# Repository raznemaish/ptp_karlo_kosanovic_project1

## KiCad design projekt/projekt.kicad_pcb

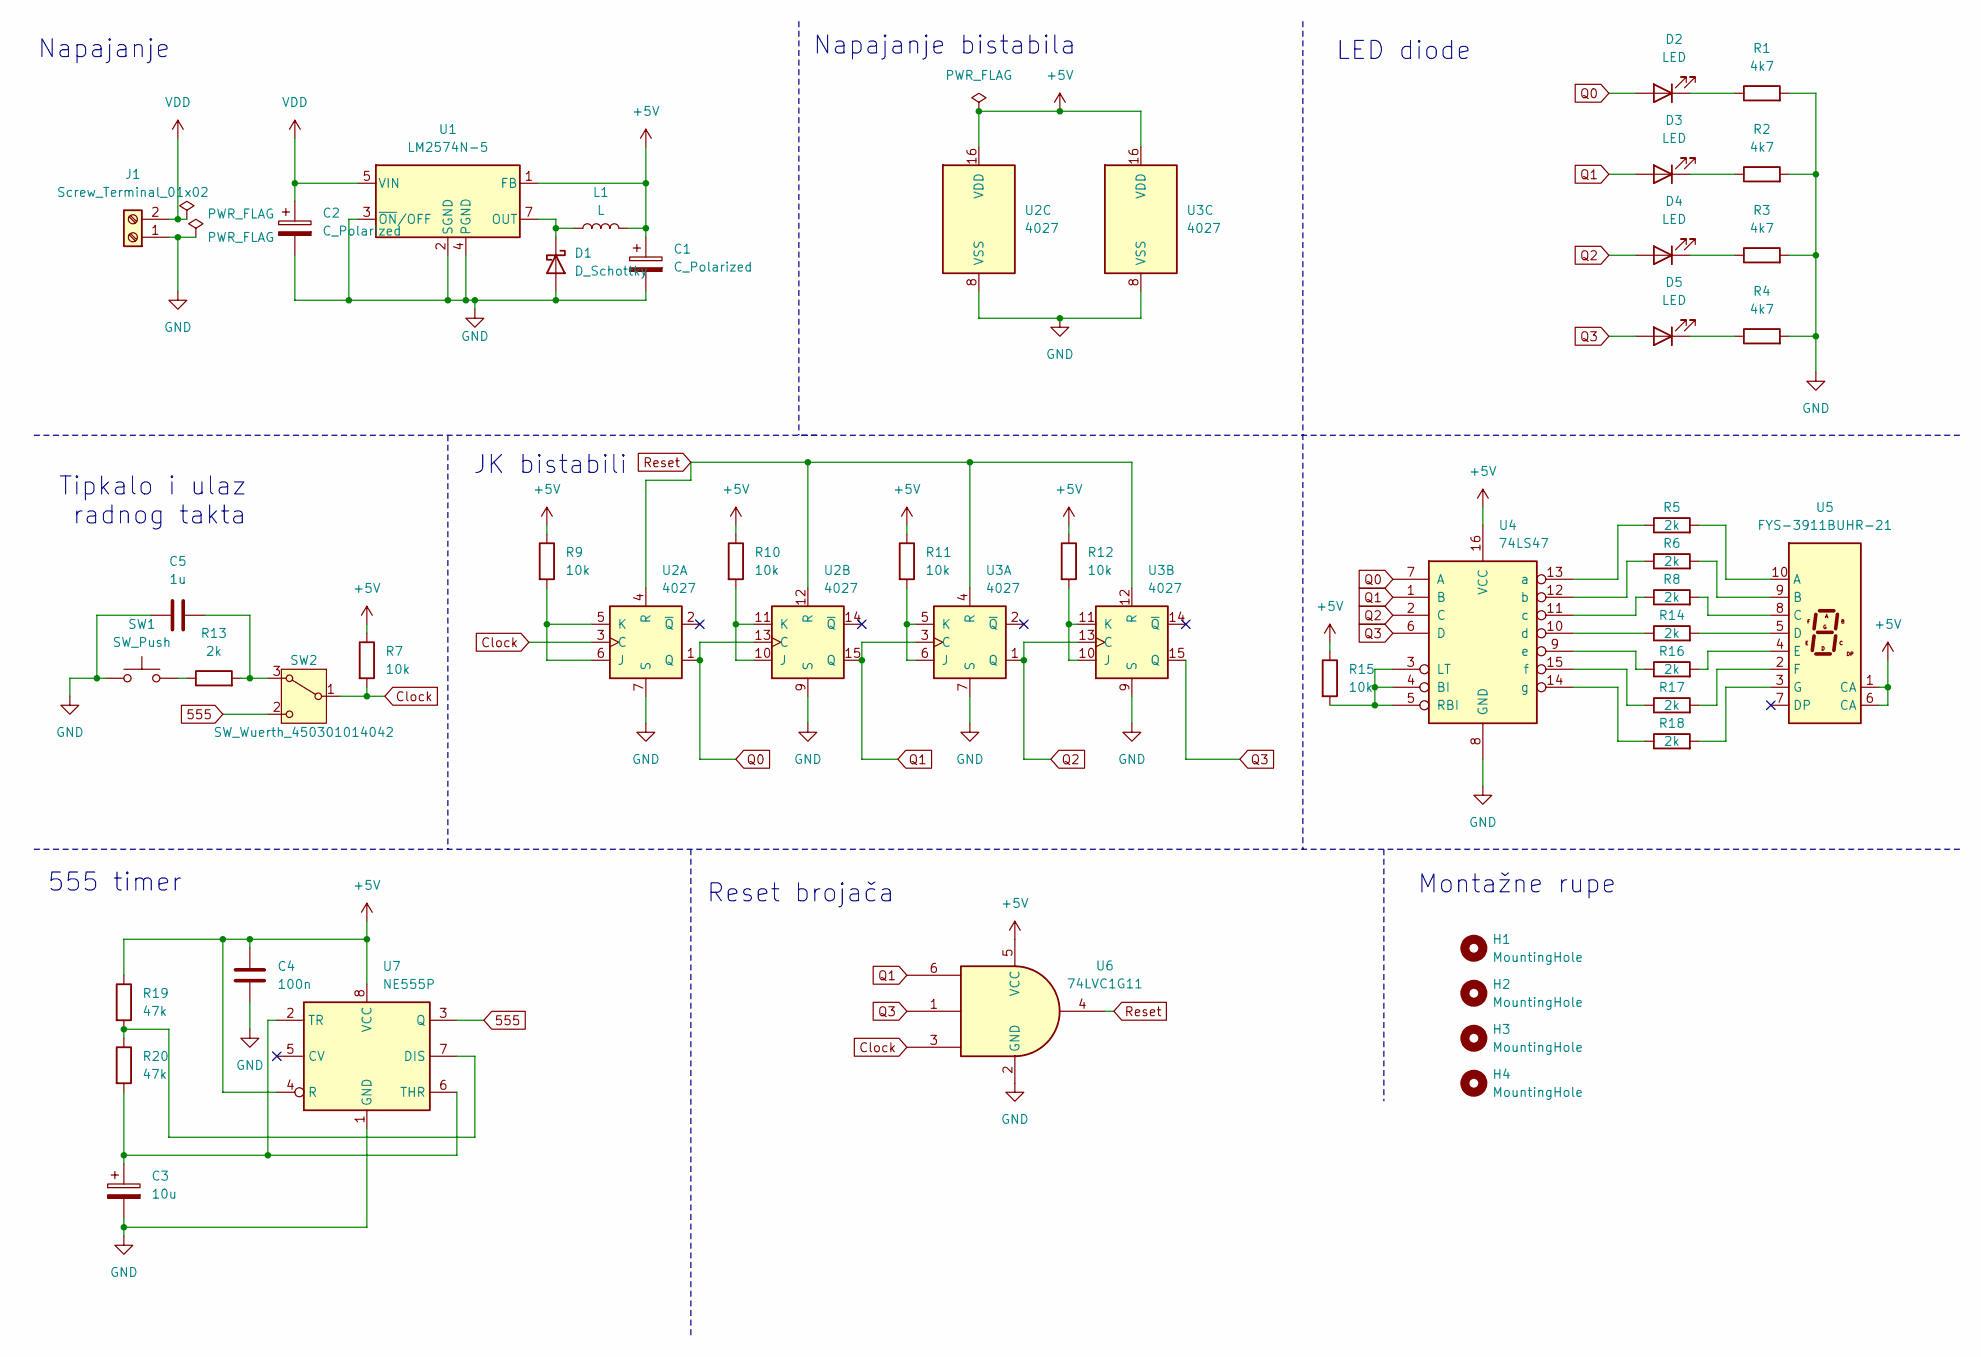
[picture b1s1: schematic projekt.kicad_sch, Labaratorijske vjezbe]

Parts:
C1, C2: C_Polarized
C3: 10u
C4: 100n
C5: 1u
D1: D_Schottky
D2, D3, D4, D5: LED
H1, H2, H3, H4: MountingHole
J1: Screw_Terminal_01x02
L1: L
R1, R2, R3, R4: 4k7
R5, R6, R8, R13, R14, R16, R17, R18: 2k
R7, R9, R10, R11, R12, R15: 10k
R19, R20: 47k
SW1: SW_Push
SW2: SW_Wuerth_450301014042; SW_Slide-03_Wuerth-WS-SLTV_10x2.5x6.4_P2.54mm
U1: LM2574N-5; DIP-8_W7.62mm
U2, U3: 4027
U4: 74LS47
U5: FYS-3911BUHR-21; HDSP-7401
U6: 74LVC1G11
U7: NE555P; DIP-8_W7.62mm

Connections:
555: SW2.2 (C), U7.3 (Q)
+5V: C1.1, C4.1, L1.2, R7.1, R9.1, R10.1, R11.1, R12.1, R15.1, R19.1, U1.1 (FB), U2.16 (VDD), U3.16 (VDD), U4.16 (VCC), U5.1 (CA), U5.6 (CA), U6.5 (VCC), U7.4 (R), U7.8 (VCC)
Clock: R7.2, SW2.1 (B), U2.3 (C), U6.3
GND: C1.2, C2.2, C3.2, C4.2, C5.1, D1.2 (A), J1.1, R1.2, R2.2, R3.2, R4.2, SW1.1, U1.2 (SGND), U1.3 (~ON/OFF), U1.4 (PGND), U2.7 (S), U2.8 (VSS), U2.9 (S), U3.7 (S), U3.8 (VSS), U3.9 (S), U4.8 (GND), U6.2 (GND), U7.1 (GND)
unnamed: D1.1 (K), L1.1, U1.7 (OUT)
unnamed: D2.1 (K), R1.1
unnamed: D3.1 (K), R2.1
unnamed: D4.1 (K), R3.1
unnamed: D5.1 (K), R4.1
unnamed: R13.1, SW1.2
unnamed: C5.2, R13.2, SW2.3 (A)
unnamed: R9.2, U2.5 (K), U2.6 (J)
unnamed: R10.2, U2.10 (J), U2.11 (K)
unnamed: R11.2, U3.5 (K), U3.6 (J)
unnamed: R12.2, U3.10 (J), U3.11 (K)
unnamed: R15.2, U4.3 (LT), U4.4 (BI), U4.5 (RBI)
unnamed: R5.1, U4.13 (a)
unnamed: R6.1, U4.12 (b)
unnamed: R8.1, U4.11 (c)
unnamed: R14.1, U4.10 (d)
unnamed: R16.1, U4.9 (e)
unnamed: R17.1, U4.15 (f)
unnamed: R18.1, U4.14 (g)
unnamed: R5.2, U5.10 (A)
unnamed: R6.2, U5.9 (B)
unnamed: R8.2, U5.8 (C)
unnamed: R14.2, U5.5 (D)
unnamed: R16.2, U5.4 (E)
unnamed: R17.2, U5.2 (F)
unnamed: R18.2, U5.3 (G)
unnamed: R19.2, R20.1, U7.7 (DIS)
unnamed: C3.1, R20.2, U7.2 (TR), U7.6 (THR)
Q0: D2.2 (A), U2.1 (Q), U2.13 (C), U4.7 (A)
Q1: D3.2 (A), U2.15 (Q), U3.3 (C), U4.1 (B), U6.6
Q2: D4.2 (A), U3.1 (Q), U3.13 (C), U4.2 (C)
Q3: D5.2 (A), U3.15 (Q), U4.6 (D), U6.1
Reset: U2.4 (R), U2.12 (R), U3.4 (R), U3.12 (R), U6.4
VDD: C2.1, J1.2, U1.5 (VIN)

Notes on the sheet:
Reset brojača
555 timer
LED diode
Napajanje bistabila
Tipkalo i ulaz radnog takta
Montažne rupe
JK bistabili
Napajanje

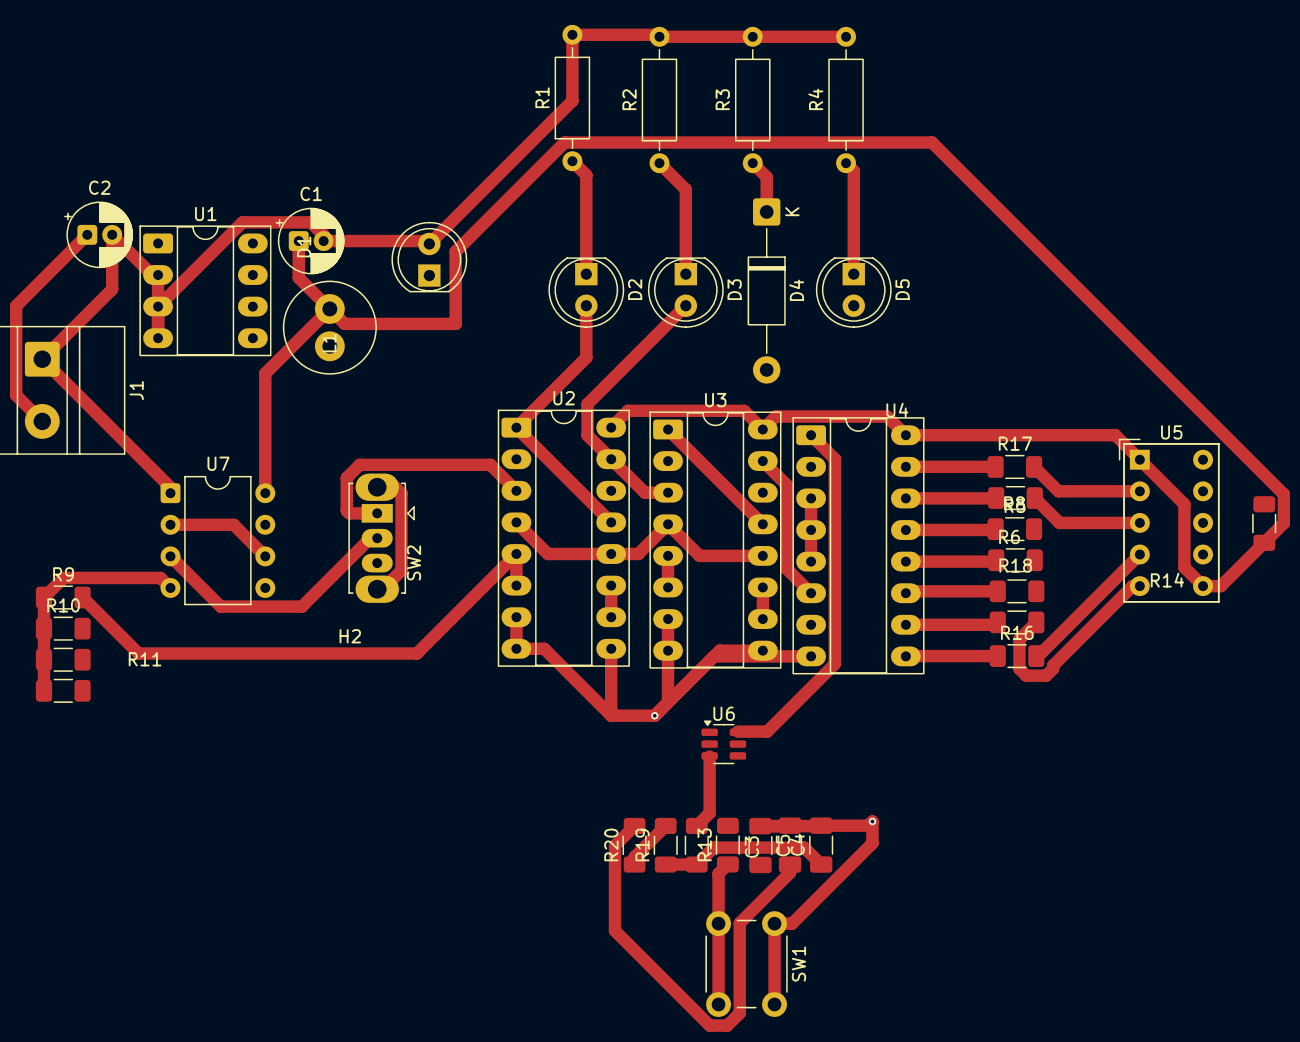
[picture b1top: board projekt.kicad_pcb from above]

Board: 2 copper layers, 45 parts (0 on the bottom side), 38 nets.

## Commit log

2025-10-29 vjezba 2
2025-11-05 a
    a
2025-11-12 cila schema
2025-11-12 schema gotovija nego prije
